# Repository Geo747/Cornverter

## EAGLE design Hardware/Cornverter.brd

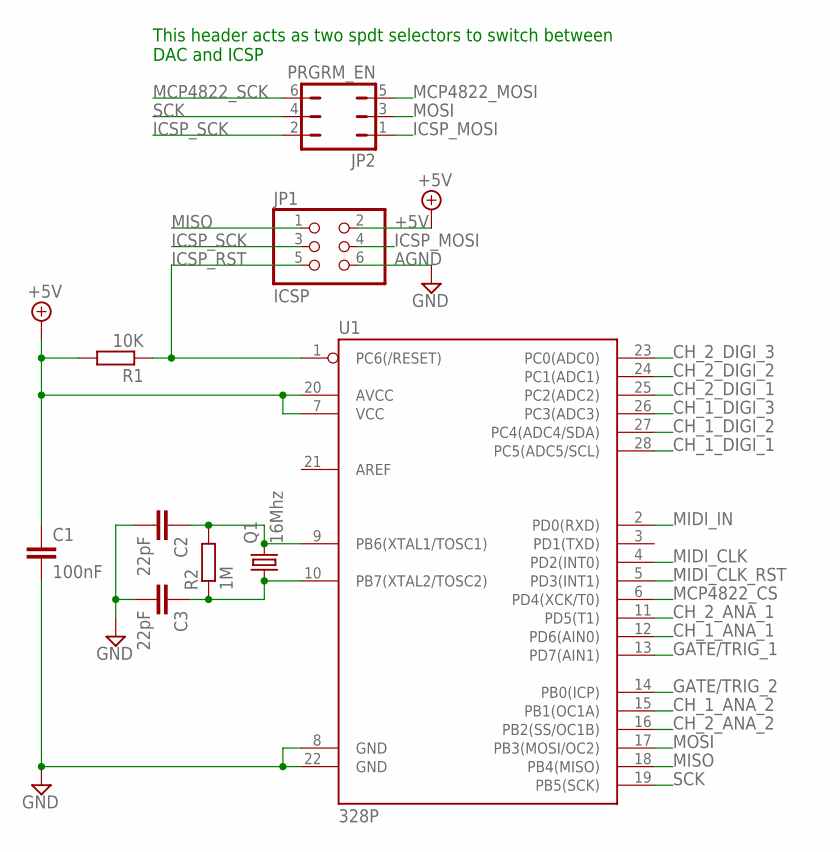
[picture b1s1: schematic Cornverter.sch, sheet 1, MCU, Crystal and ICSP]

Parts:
C1: 100nF; C1206
C2, C3: 22pF; C1206
JP1: ICSP; 2X03
JP2: PRGRM_EN; JP3Q
Q1: 16Mhz; HC49/S
R1: 10K; R1206
R2: 1M; R1206
U1: 328P; DIP28

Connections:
+5V: C1.1, JP1.2, R1.2, U1.7 (VCC), U1.20 (AVCC); also elsewhere on the board
AGND: C1.2, C2.2, C3.2, JP1.6, U1.8 (GND), U1.22 (GND); also elsewhere on the board
CH_1_ANA_1: U1.12 (PD6(AIN0)); also elsewhere on the board
CH_1_ANA_2: U1.15 (PB1(OC1A)); also elsewhere on the board
CH_1_DIGI_1: U1.28 (PC5(ADC5/SCL)); also elsewhere on the board
CH_1_DIGI_2: U1.27 (PC4(ADC4/SDA)); also elsewhere on the board
CH_1_DIGI_3: U1.26 (PC3(ADC3)); also elsewhere on the board
CH_2_ANA_1: U1.11 (PD5(T1)); also elsewhere on the board
CH_2_ANA_2: U1.16 (PB2(SS/OC1B)); also elsewhere on the board
CH_2_DIGI_1: U1.25 (PC2(ADC2)); also elsewhere on the board
CH_2_DIGI_2: U1.24 (PC1(ADC1)); also elsewhere on the board
CH_2_DIGI_3: U1.23 (PC0(ADC0)); also elsewhere on the board
GATE/TRIG_1: U1.13 (PD7(AIN1)); also elsewhere on the board
GATE/TRIG_2: U1.14 (PB0(ICP)); also elsewhere on the board
ICSP_MOSI: JP1.4, JP2.1
ICSP_RST: JP1.5, R1.1, U1.1 (PC6(/RESET))
ICSP_SCK: JP1.3, JP2.2
MCP4822_CS: U1.6 (PD4(XCK/T0)); also elsewhere on the board
MCP4822_MOSI: JP2.5; also elsewhere on the board
MCP4822_SCK: JP2.6; also elsewhere on the board
MIDI_CLK: U1.4 (PD2(INT0)); also elsewhere on the board
MIDI_CLK_RST: U1.5 (PD3(INT1)); also elsewhere on the board
MIDI_IN: U1.2 (PD0(RXD)); also elsewhere on the board
MISO: JP1.1, U1.18 (PB4(MISO))
MOSI: JP2.3, U1.17 (PB3(MOSI/OC2))
unnamed: C3.1, Q1.1, R2.1, U1.10 (PB7(XTAL2/TOSC2))
unnamed: C2.1, Q1.2, R2.2, U1.9 (PB6(XTAL1/TOSC1))
SCK: JP2.4, U1.19 (PB5(SCK))

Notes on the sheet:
This header acts as two spdt selectors to switch between DAC and ICSP

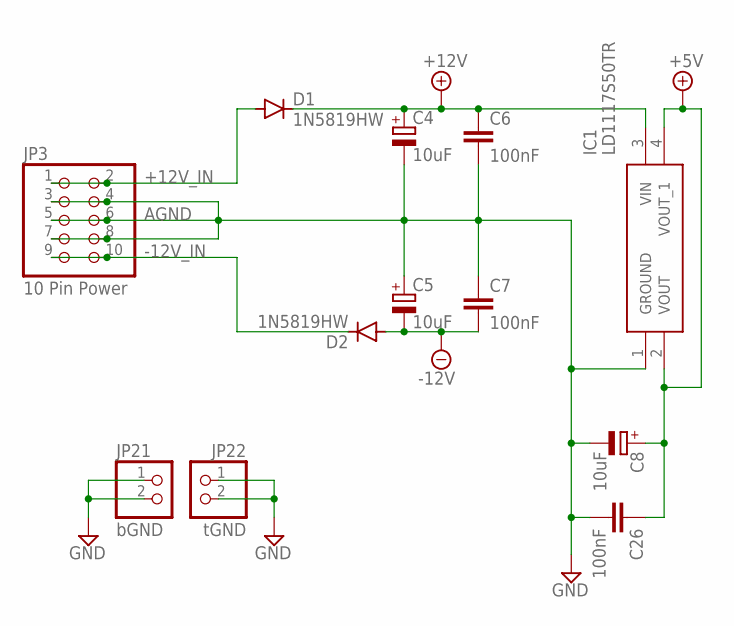
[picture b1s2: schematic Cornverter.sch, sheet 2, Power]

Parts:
C4, C5, C8: 10uF; E2-5
C6, C7, C26: 100nF; C1206
D1, D2: 1N5819HW; SOD123
IC1: LD1117S50TR; SOT230P700X190-4N
JP3: 10 Pin Power; 2X05
JP21: bGND; 1X02
JP22: tGND; 1X02

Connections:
+5V: C8.+, C26.1, IC1.2 (VOUT), IC1.4 (VOUT_1); also elsewhere on the board
+12V: C4.+, C6.1, D1.C, IC1.3 (VIN); also elsewhere on the board
+12V_IN: D1.A, JP3.1, JP3.2
-12V: C5.-, C7.2, D2.A; also elsewhere on the board
-12V_IN: D2.C, JP3.9, JP3.10
AGND: C4.-, C5.+, C6.2, C7.1, C8.-, C26.2, IC1.1 (GROUND), JP3.3, JP3.4, JP3.5, JP3.6, JP3.7, JP3.8, JP21.1, JP21.2, JP22.1, JP22.2; also elsewhere on the board

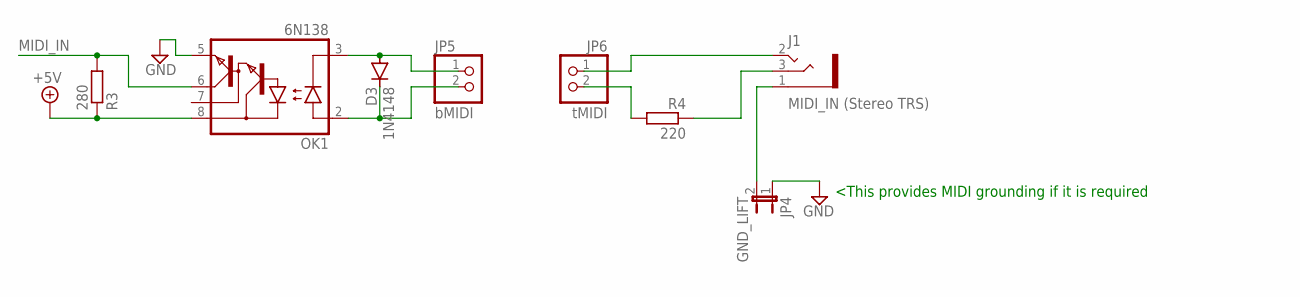
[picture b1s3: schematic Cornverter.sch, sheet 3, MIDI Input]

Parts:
D3: 1N4148; DO35-7
J1: MIDI_IN (Stereo TRS); WQP-PJ301M-12-ST_JACK
JP4: GND_LIFT; JP1
JP5: bMIDI; 1X02
JP6: tMIDI; 1X02
OK1: 6N138; DIL08
R3: 280; R1206
R4: 220; R1206

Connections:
+5V: OK1.8 (VCC), R3.1; also elsewhere on the board
AGND: JP4.1, OK1.5 (GND); also elsewhere on the board
MIDI_IN: OK1.6 (VO), R3.2; also elsewhere on the board
unnamed: J1.1, JP4.2
unnamed: J1.3, R4.1
unnamed: D3.A, JP5.1, OK1.3 (C)
unnamed: D3.C, JP5.2, OK1.2 (A)
unnamed: JP6.2, R4.2
unnamed: J1.2, JP6.1

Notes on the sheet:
<This provides MIDI grounding if it is required

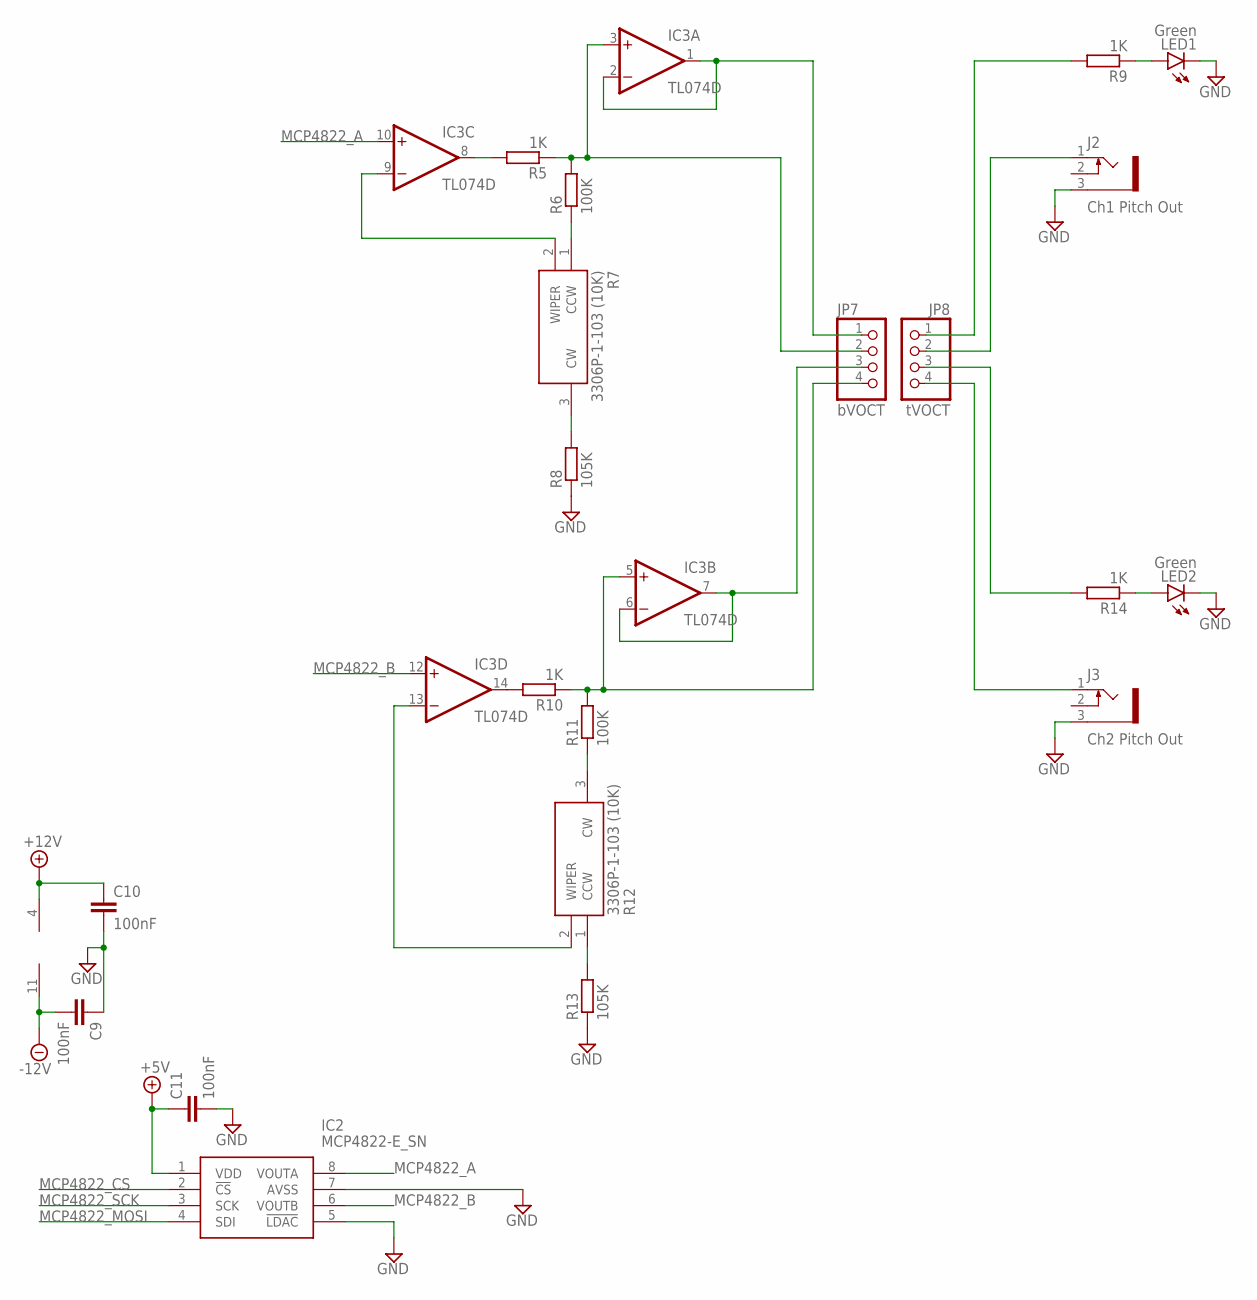
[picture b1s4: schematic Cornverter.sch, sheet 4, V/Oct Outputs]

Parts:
C9, C10, C11: 100nF; C1206
IC2: MCP4822-E_SN; SOIC127P600X175-8N
IC3: TL074D; SO14
J2: Ch1 Pitch Out; WQP-PJ301M-12_JACK
J3: Ch2 Pitch Out; WQP-PJ301M-12_JACK
JP7: bVOCT; 1X04
JP8: tVOCT; 1X04
LED1, LED2: Green; LED3MM
R5, R9, R10, R14: 1K; R1206
R6, R11: 100K; R1206
R7, R12: 3306P-1-103 (10K); 3306P1103
R8, R13: 105K; R1206

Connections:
+5V: C11.1, IC2.1 (VDD); also elsewhere on the board
+12V: C10.1, IC3.4 (V+); also elsewhere on the board
-12V: C9.2, IC3.11 (V-); also elsewhere on the board
AGND: C9.1, C10.2, C11.2, IC2.5 (!LDAC), IC2.7 (AVSS), J2.3 (1), J3.3 (1), LED1.C, LED2.C, R8.1, R13.1; also elsewhere on the board
MCP4822_A: IC2.8 (VOUTA), IC3.10 (+IN)
MCP4822_B: IC2.6 (VOUTB), IC3.12 (+IN)
MCP4822_CS: IC2.2 (!CS); also elsewhere on the board
MCP4822_MOSI: IC2.4 (SDI); also elsewhere on the board
MCP4822_SCK: IC2.3 (SCK); also elsewhere on the board
unnamed: R6.1, R7.1 (CCW)
unnamed: R7.3 (CW), R8.2
unnamed: R12.1 (CCW), R13.2
unnamed: R11.1, R12.3 (CW)
unnamed: LED1.A, R9.1
unnamed: IC3.1 (OUT), IC3.2 (-IN), JP7.1
unnamed: LED2.A, R14.1
unnamed: IC3.6 (-IN), IC3.7 (OUT), JP7.3
unnamed: IC3.9 (-IN), R7.2 (WIPER)
unnamed: IC3.3 (+IN), JP7.2, R5.1, R6.2
unnamed: IC3.13 (-IN), R12.2 (WIPER)
unnamed: IC3.5 (+IN), JP7.4, R10.1, R11.2
unnamed: IC3.14 (OUT), R10.2
unnamed: IC3.8 (OUT), R5.2
unnamed: JP8.1, R9.2
unnamed: J2.1 (2), JP8.2
unnamed: JP8.3, R14.2
unnamed: J3.1 (2), JP8.4

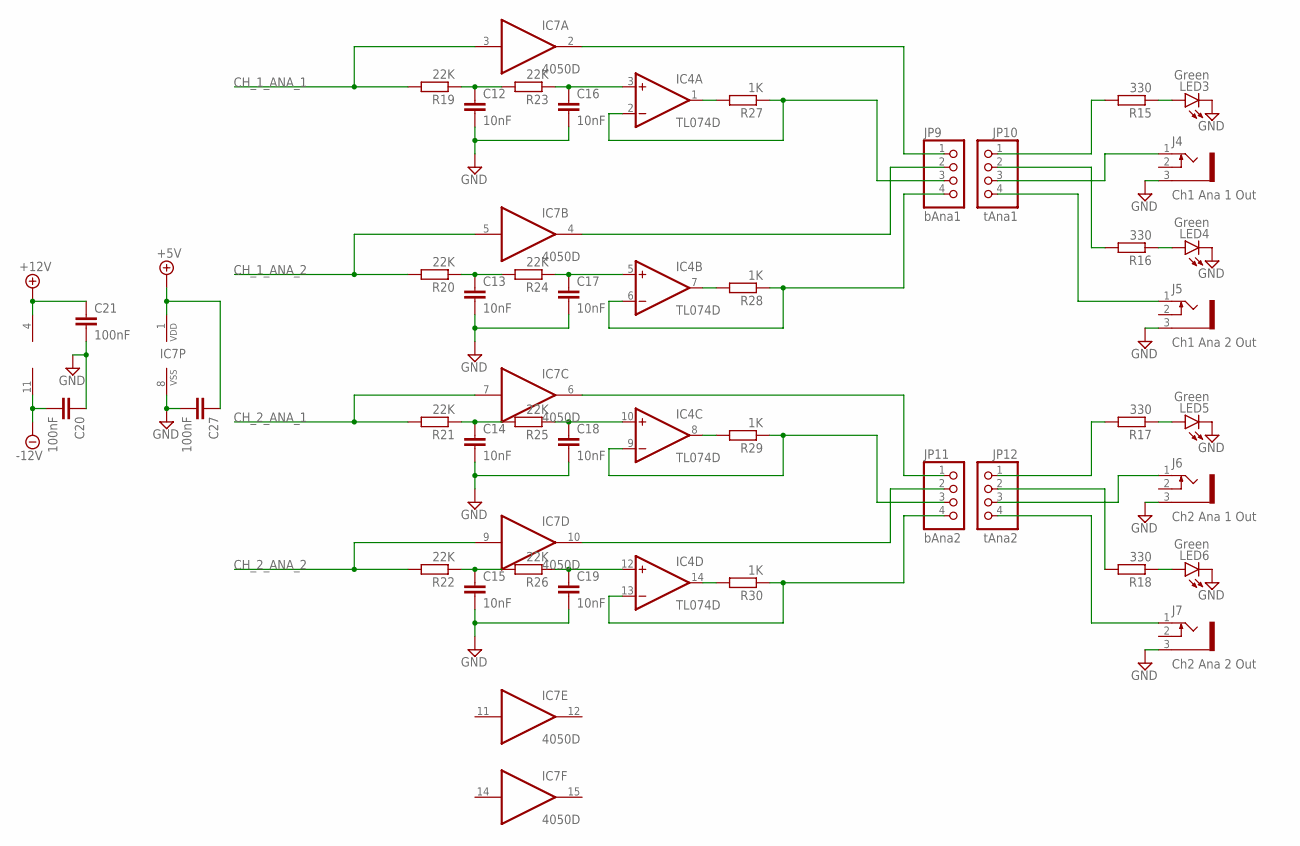
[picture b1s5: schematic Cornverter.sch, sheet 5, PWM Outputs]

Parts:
C12, C13, C14, C15, C16, C17, C18, C19: 10nF; C1206
C20, C21, C27: 100nF; C1206
IC4: TL074D; SO14
IC7: 4050D; SO16
J4: Ch1 Ana 1 Out; WQP-PJ301M-12_JACK
J5: Ch1 Ana 2 Out; WQP-PJ301M-12_JACK
J6: Ch2 Ana 1 Out; WQP-PJ301M-12_JACK
J7: Ch2 Ana 2 Out; WQP-PJ301M-12_JACK
JP9: bAna1; 1X04
JP10: tAna1; 1X04
JP11: bAna2; 1X04
JP12: tAna2; 1X04
LED3, LED4, LED5, LED6: Green; LED3MM
R15, R16, R17, R18: 330; R1206
R19, R20, R21, R22, R23, R24, R25, R26: 22K; R1206
R27, R28, R29, R30: 1K; R1206

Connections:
+5V: C27.1, IC7.1 (VDD); also elsewhere on the board
+12V: C21.1, IC4.4 (V+); also elsewhere on the board
-12V: C20.2, IC4.11 (V-); also elsewhere on the board
AGND: C12.2, C13.2, C14.2, C15.2, C16.2, C17.2, C18.2, C19.2, C20.1, C21.2, C27.2, IC7.8 (VSS), J4.3 (1), J5.3 (1), J6.3 (1), J7.3 (1), LED3.C, LED4.C, LED5.C, LED6.C; also elsewhere on the board
CH_1_ANA_1: IC7.3 (I), R19.2; also elsewhere on the board
CH_1_ANA_2: IC7.5 (I), R20.2; also elsewhere on the board
CH_2_ANA_1: IC7.7 (I), R21.2; also elsewhere on the board
CH_2_ANA_2: IC7.9 (I), R22.2; also elsewhere on the board
unnamed: C13.1, R20.1, R24.2
unnamed: LED4.A, R16.1
unnamed: IC4.6 (-IN), JP9.4, R28.1
unnamed: C12.1, R19.1, R23.2
unnamed: LED3.A, R15.1
unnamed: IC4.7 (OUT), R28.2
unnamed: C17.1, IC4.5 (+IN), R24.1
unnamed: IC4.1 (OUT), R27.2
unnamed: C14.1, R21.1, R25.2
unnamed: LED5.A, R17.1
unnamed: IC4.9 (-IN), JP11.3, R29.1
unnamed: IC4.8 (OUT), R29.2
unnamed: C16.1, IC4.3 (+IN), R23.1
unnamed: C18.1, IC4.10 (+IN), R25.1
unnamed: C15.1, R22.1, R26.2
unnamed: LED6.A, R18.1
unnamed: IC4.13 (-IN), JP11.4, R30.1
unnamed: IC4.14 (OUT), R30.2
unnamed: IC4.2 (-IN), JP9.3, R27.1
unnamed: C19.1, IC4.12 (+IN), R26.1
unnamed: JP10.1, R15.2
unnamed: J4.1 (2), JP10.3
unnamed: J5.1 (2), JP10.4
unnamed: JP12.1, R17.2
unnamed: JP12.2, R18.2
unnamed: J6.1 (2), JP12.3
unnamed: J7.1 (2), JP12.4
unnamed: JP10.2, R16.2
unnamed: IC7.2 (O), JP9.1
unnamed: IC7.4 (O), JP9.2
unnamed: IC7.6 (O), JP11.1
unnamed: IC7.10 (O), JP11.2

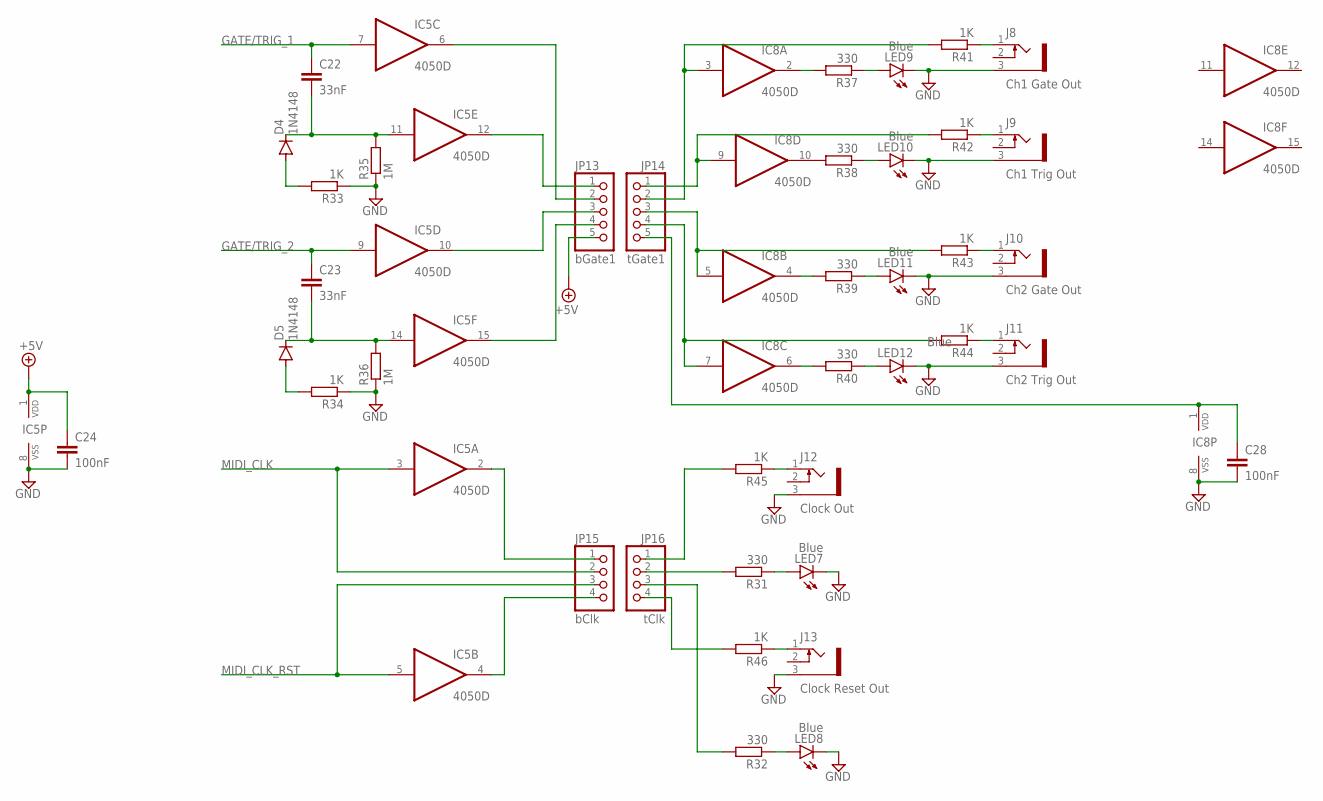
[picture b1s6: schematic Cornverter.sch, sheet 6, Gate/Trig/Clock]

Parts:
C22, C23: 33nF; C1206
C24, C28: 100nF; C1206
D4, D5: 1N4148; DO35-7
IC5, IC8: 4050D; SO16
J8: Ch1 Gate Out; WQP-PJ301M-12_JACK
J9: Ch1 Trig Out; WQP-PJ301M-12_JACK
J10: Ch2 Gate Out; WQP-PJ301M-12_JACK
J11: Ch2 Trig Out; WQP-PJ301M-12_JACK
J12: Clock Out; WQP-PJ301M-12_JACK
J13: Clock Reset Out; WQP-PJ301M-12_JACK
JP13: bGate1; 1X05
JP14: tGate1; 1X05
JP15: bClk; 1X04
JP16: tClk; 1X04
LED7, LED8, LED9, LED10, LED11, LED12: Blue; LED3MM
R31, R32, R37, R38, R39, R40: 330; R1206
R33, R34, R41, R42, R43, R44, R45, R46: 1K; R1206
R35, R36: 1M; R1206

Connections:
+5V: C24.1, IC5.1 (VDD), JP13.5; also elsewhere on the board
AGND: C24.2, C28.2, IC5.8 (VSS), IC8.8 (VSS), J8.3 (1), J9.3 (1), J10.3 (1), J11.3 (1), J12.3 (1), J13.3 (1), LED7.C, LED8.C, LED9.C, LED10.C, LED11.C, LED12.C, R33.1, R34.1, R35.1, R36.1; also elsewhere on the board
GATE/TRIG_1: C22.1, IC5.7 (I); also elsewhere on the board
GATE/TRIG_2: C23.1, IC5.9 (I); also elsewhere on the board
MIDI_CLK: IC5.3 (I), JP15.2; also elsewhere on the board
MIDI_CLK_RST: IC5.5 (I), JP15.3; also elsewhere on the board
unnamed: C22.2, D4.C, IC5.11 (I), R35.2
unnamed: D4.A, R33.2
unnamed: IC8.7 (I), JP14.4, R44.2
unnamed: LED12.A, R40.1
unnamed: LED11.A, R39.1
unnamed: IC8.5 (I), JP14.3, R43.2
unnamed: J11.1 (2), R44.1
unnamed: J10.1 (2), R43.1
unnamed: C23.2, D5.C, IC5.14 (I), R36.2
unnamed: D5.A, R34.2
unnamed: IC8.9 (I), JP14.1, R42.2
unnamed: LED10.A, R38.1
unnamed: LED9.A, R37.1
unnamed: IC8.3 (I), JP14.2, R41.2
unnamed: LED7.A, R31.1
unnamed: J12.1 (2), R45.1
unnamed: IC5.2 (O), JP15.1
unnamed: J13.1 (2), R46.1
unnamed: IC5.4 (O), JP15.4
unnamed: LED8.A, R32.1
unnamed: J9.1 (2), R42.1
unnamed: J8.1 (2), R41.1
unnamed: IC8.2 (O), R37.2
unnamed: IC5.6 (O), JP13.2
unnamed: IC5.12 (O), JP13.1
unnamed: IC5.15 (O), JP13.4
unnamed: IC5.10 (O), JP13.3
unnamed: JP16.1, R45.2
unnamed: JP16.2, R31.2
unnamed: JP16.4, R46.2
unnamed: JP16.3, R32.2
unnamed: IC8.10 (O), R38.2
unnamed: IC8.4 (O), R39.2
unnamed: IC8.6 (O), R40.2
TOP+5V: C28.1, IC8.1 (VDD), JP14.5

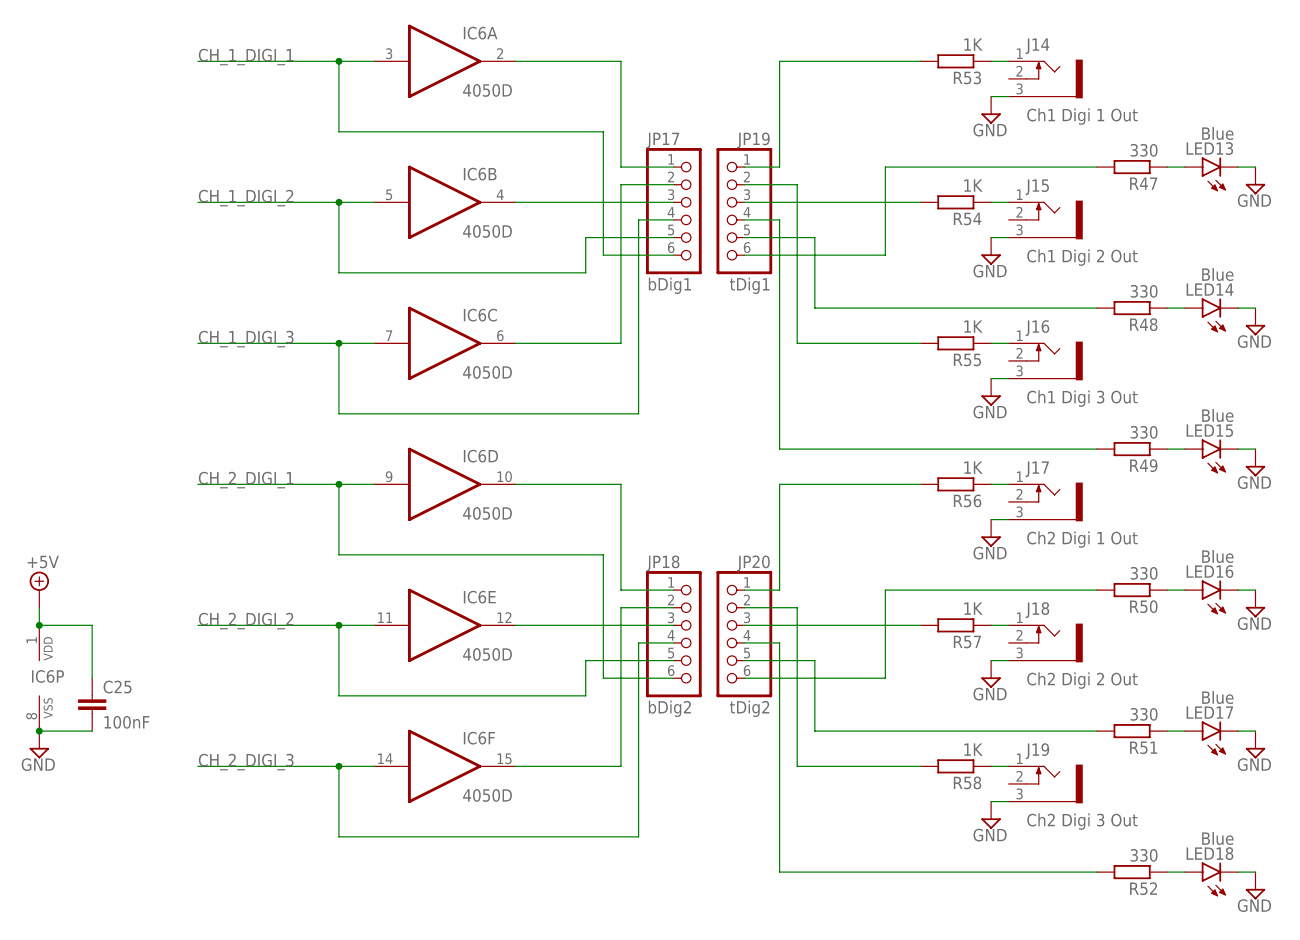
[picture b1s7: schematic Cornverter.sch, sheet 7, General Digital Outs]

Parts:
C25: 100nF; C1206
IC6: 4050D; SO16
J14: Ch1 Digi 1 Out; WQP-PJ301M-12_JACK
J15: Ch1 Digi 2 Out; WQP-PJ301M-12_JACK
J16: Ch1 Digi 3 Out; WQP-PJ301M-12_JACK
J17: Ch2 Digi 1 Out; WQP-PJ301M-12_JACK
J18: Ch2 Digi 2 Out; WQP-PJ301M-12_JACK
J19: Ch2 Digi 3 Out; WQP-PJ301M-12_JACK
JP17: bDig1; 1X06
JP18: bDig2; 1X06
JP19: tDig1; 1X06
JP20: tDig2; 1X06
LED13, LED14, LED15, LED16, LED17, LED18: Blue; LED3MM
R47, R48, R49, R50, R51, R52: 330; R1206
R53, R54, R55, R56, R57, R58: 1K; R1206

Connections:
+5V: C25.1, IC6.1 (VDD); also elsewhere on the board
AGND: C25.2, IC6.8 (VSS), J14.3 (1), J15.3 (1), J16.3 (1), J17.3 (1), J18.3 (1), J19.3 (1), LED13.C, LED14.C, LED15.C, LED16.C, LED17.C, LED18.C; also elsewhere on the board
CH_1_DIGI_1: IC6.3 (I), JP17.6; also elsewhere on the board
CH_1_DIGI_2: IC6.5 (I), JP17.5; also elsewhere on the board
CH_1_DIGI_3: IC6.7 (I), JP17.4; also elsewhere on the board
CH_2_DIGI_1: IC6.9 (I), JP18.6; also elsewhere on the board
CH_2_DIGI_2: IC6.11 (I), JP18.5; also elsewhere on the board
CH_2_DIGI_3: IC6.14 (I), JP18.4; also elsewhere on the board
unnamed: LED15.A, R49.1
unnamed: J16.1 (2), R55.1
unnamed: JP19.1, R53.2
unnamed: J17.1 (2), R56.1
unnamed: JP19.6, R47.2
unnamed: LED16.A, R50.1
unnamed: LED17.A, R51.1
unnamed: J18.1 (2), R57.1
unnamed: JP19.3, R54.2
unnamed: J19.1 (2), R58.1
unnamed: JP19.4, R49.2
unnamed: LED13.A, R47.1
unnamed: J14.1 (2), R53.1
unnamed: JP19.2, R55.2
unnamed: J15.1 (2), R54.1
unnamed: JP19.5, R48.2
unnamed: LED14.A, R48.1
unnamed: LED18.A, R52.1
unnamed: JP20.1, R56.2
unnamed: JP20.6, R50.2
unnamed: JP20.2, R58.2
unnamed: JP20.5, R51.2
unnamed: JP20.3, R57.2
unnamed: JP20.4, R52.2
unnamed: IC6.2 (O), JP17.1
unnamed: IC6.6 (O), JP17.2
unnamed: IC6.10 (O), JP18.1
unnamed: IC6.15 (O), JP18.2
unnamed: IC6.12 (O), JP18.3
unnamed: IC6.4 (O), JP17.3

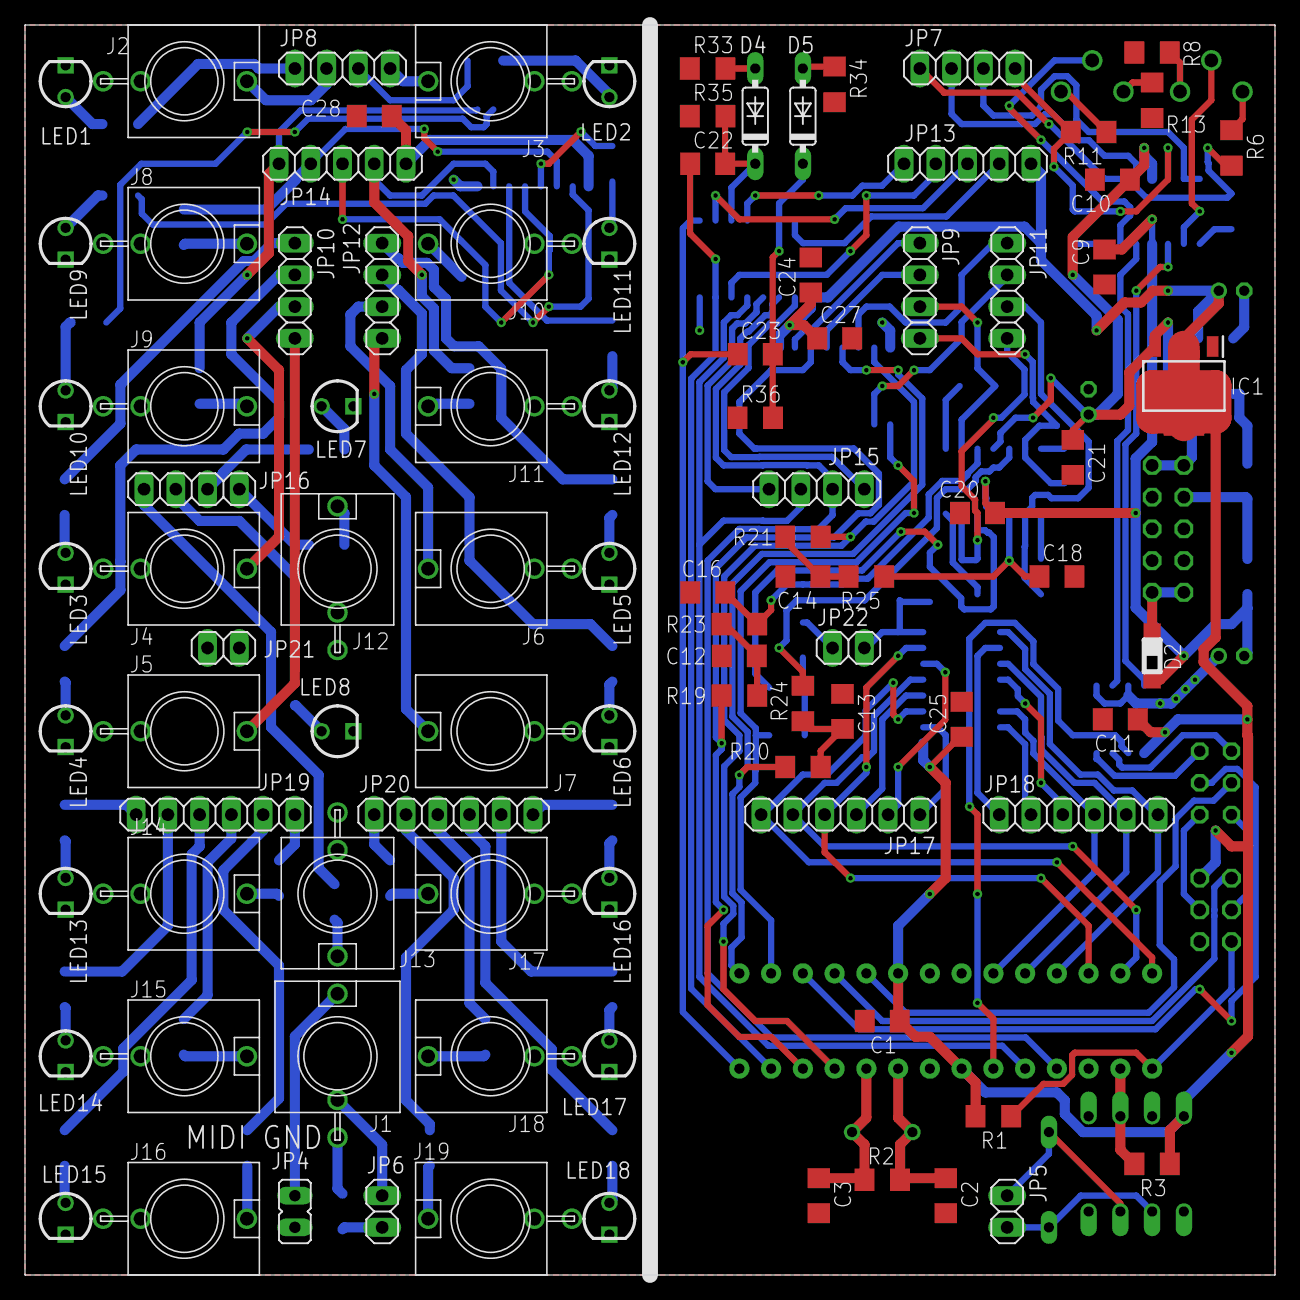
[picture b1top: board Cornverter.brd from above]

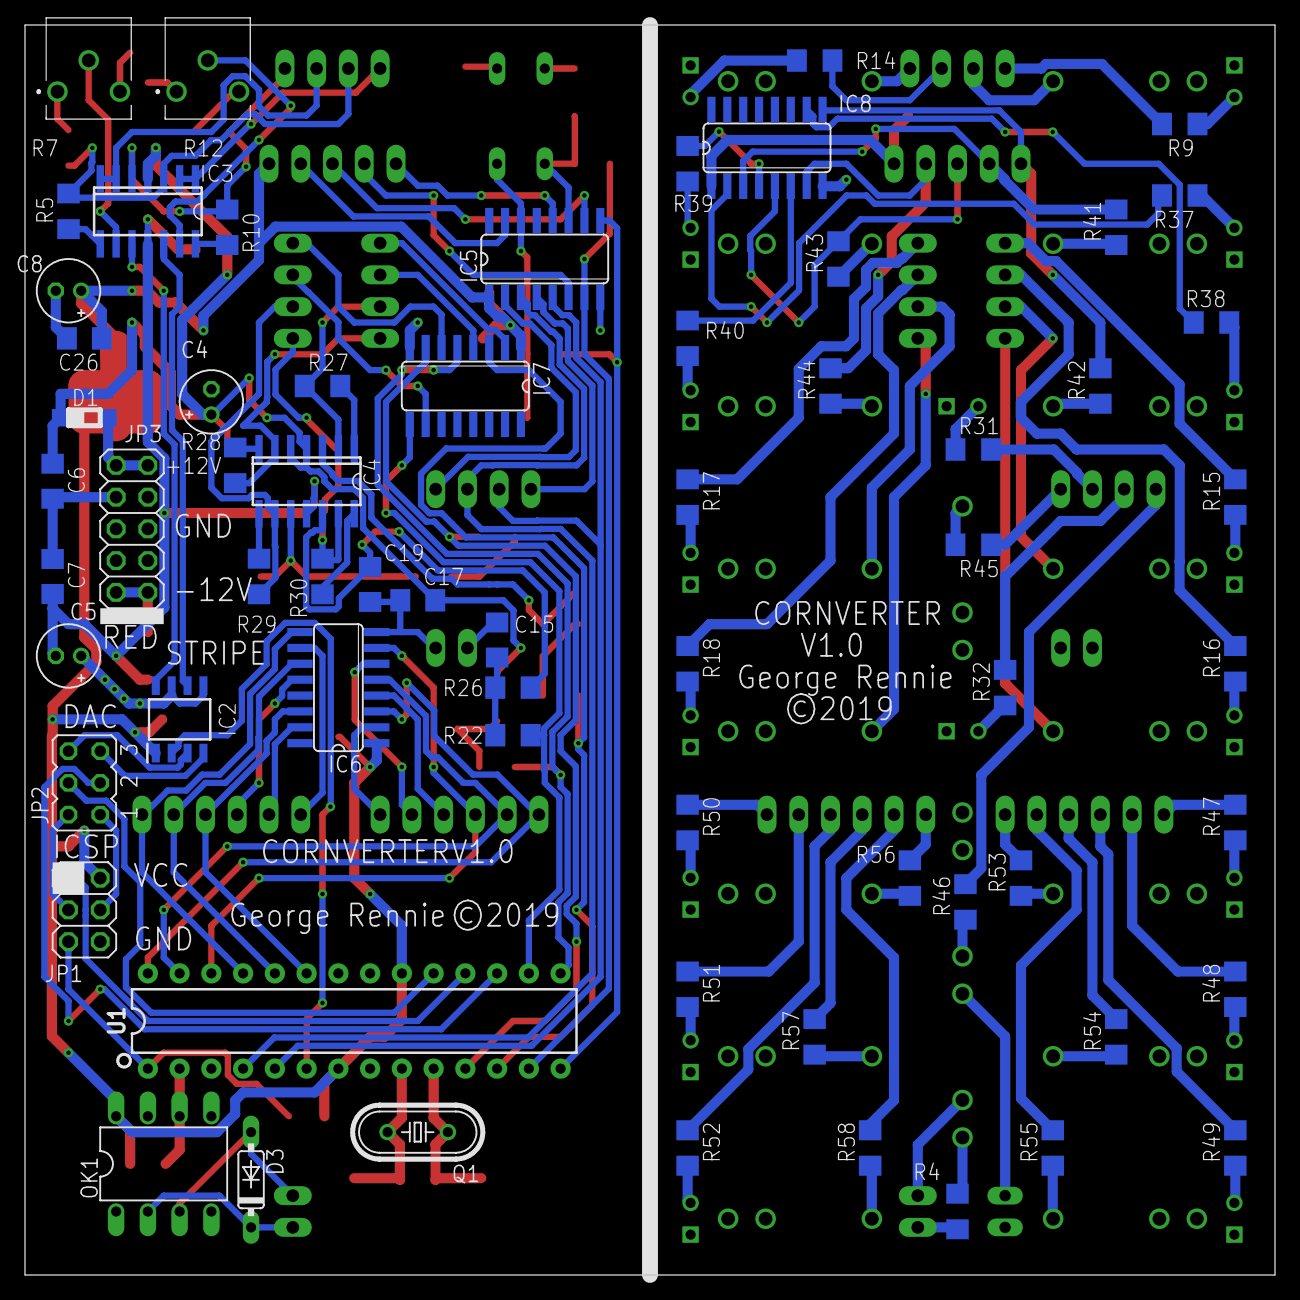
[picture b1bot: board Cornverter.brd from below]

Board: 2 copper layers, 100.0 x 100.0 mm, 161 parts (65 on the bottom side), 155 nets.

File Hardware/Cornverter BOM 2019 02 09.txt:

Qty	Value	Device	Package	Parts	Description	DESCRIPTION	HEIGHT	MANUFACTURER_NAME	MANUFACTURER_PART_NUMBER	MF	MOUSER_PART_NUMBER	MPN	OC_FARNELL	OC_NEWARK	PROD_ID	SPICEPREFIX	VALUE
1	bGND	PINHD-1X2	1X02	JP21	PIN HEADER												
1	bMIDI	PINHD-1X2	1X02	JP5	PIN HEADER												
1	tGND	PINHD-1X2	1X02	JP22	PIN HEADER												
1	tMIDI	PINHD-1X2	1X02	JP6	PIN HEADER												
1	bAna1	PINHD-1X4	1X04	JP9	PIN HEADER												
1	bAna2	PINHD-1X4	1X04	JP11	PIN HEADER												
1	bClk	PINHD-1X4	1X04	JP15	PIN HEADER												
1	bVOCT	PINHD-1X4	1X04	JP7	PIN HEADER												
1	tAna1	PINHD-1X4	1X04	JP10	PIN HEADER												
1	tAna2	PINHD-1X4	1X04	JP12	PIN HEADER												
1	tClk	PINHD-1X4	1X04	JP16	PIN HEADER												
1	tVOCT	PINHD-1X4	1X04	JP8	PIN HEADER												
1	bGate1	PINHD-1X5	1X05	JP13	PIN HEADER												
1	tGate1	PINHD-1X5	1X05	JP14	PIN HEADER												
1	bDig1	PINHD-1X6	1X06	JP17	PIN HEADER												
1	bDig2	PINHD-1X6	1X06	JP18	PIN HEADER												
1	tDig1	PINHD-1X6	1X06	JP19	PIN HEADER												
1	tDig2	PINHD-1X6	1X06	JP20	PIN HEADER												
1	ICSP	PINHD-2X3	2X03	JP1	PIN HEADER												
1	10 Pin Power	PINHD-2X5	2X05	JP3	PIN HEADER												
2	3306P-1-103 (10K)	3306P-1-103	3306P1103	"R7, R12"	"3306P 1-turn cermet trimmer,10K 300mW Bourns 3306P Series Through Hole Cermet Trimmer Resistor with Pin Terminations, 10k 25% 1/5W 250ppm/C Top Adjust"	"3306P 1-turn cermet trimmer,10K 300mW Bourns 3306P Series Through Hole Cermet Trimmer Resistor with Pin Terminations, 10k 25% 1/5W 250ppm/C Top Adjust"	8mm	Bourns	3306P-1-103		652-3306P-1-103						
13	100nF	C-EUC1206	C1206	"C1, C6, C7, C9, C10, C11, C20, C21, C24, C25, C27, C28, C26"	"CAPACITOR, European symbol"											C	
8	10nF	C-EUC1206	C1206	"C12, C13, C14, C15, C16, C17, C18, C19"	"CAPACITOR, European symbol"											C	
2	22pF	C-EUC1206	C1206	"C2, C3"	"CAPACITOR, European symbol"											C	
2	33nF	C-EUC1206	C1206	"C22, C23"	"CAPACITOR, European symbol"											C	
1	6N138	6N138	DIL08	OK1	MOTOROLA OPTO COUPLER					VISHAY/TELEFUNKEN		6N138	9860150	35K5294		X	
1	328P	ATMEGA328P_PDIP	DIP28	U1	Atmel 328P										IC-09136		328P
3	1N4148	1N4148DO35-7	DO35-7	"D3, D4, D5"	DIODE												
3	10uF	CPOL-EUE2-5	E2-5	"C4, C5, C8"	"POLARIZED CAPACITOR, European symbol"											C	
1	16Mhz	CRYSTALHC49S	HC49/S	Q1	CRYSTAL								1667008	unknown			
1	GND_LIFT	JP1E	JP1	JP4	JUMPER												
1	PRGRM_EN	JP3Q	JP3Q	JP2	JUMPER												
12	Blue	LED3MM	LED3MM	"LED7, LED8, LED9, LED10, LED11, LED12, LED13, LED14, LED15, LED16, LED17, LED18"	3MM LED with clearer silkscreen than stock												
6	Green	LED3MM	LED3MM	"LED1, LED2, LED3, LED4, LED5, LED6"	3MM LED with clearer silkscreen than stock												
2	100K	R-EU_R1206	R1206	"R6, R11"	"RESISTOR, European symbol"											R	
2	105K	R-EU_R1206	R1206	"R8, R13"	"RESISTOR, European symbol"											R	
1	10K	R-EU_R1206	R1206	R1	"RESISTOR, European symbol"												
22	1K	R-EU_R1206	R1206	"R5, R9, R10, R14, R27, R28, R29, R30, R33, R34, R41, R42, R43, R44, R45, R46, R53, R54, R55, R56, R57, R58"	"RESISTOR, European symbol"											R	
3	1M	R-EU_R1206	R1206	"R2, R35, R36"	"RESISTOR, European symbol"											R	
2	220	R-EU_R1206	R1206	"R3, R4"	"RESISTOR, European symbol"											R	
8	22K	R-EU_R1206	R1206	"R19, R20, R21, R22, R23, R24, R25, R26"	"RESISTOR, European symbol"											R	
16	330	R-EU_R1206	R1206	"R15, R16, R17, R18, R31, R32, R37, R38, R39, R40, R47, R48, R49, R50, R51, R52"	"RESISTOR, European symbol"											R	
2	TL074D	TL074D	SO14	"IC3, IC4"	OP AMP												
4	4050D	4050D	SO16	"IC5, IC6, IC7, IC8"	Hex non-inverting BUFFER												
2	1N5819HW	DIODE-SOD123	SOD123	"D1, D2"	DIODE												
1	MCP4822-E_SN	MCP4822-E_SN	SOIC127P600X175-8N	IC2	D/A Converter 12-Bit 2ch SPI SOIC8	D/A Converter 12-Bit 2ch SPI SOIC8	1.75mm	Microchip	MCP4822-E/SN		579-MCP4822-E/SN						
1	LD1117S50TR	LD1117S50TR	SOT230P700X190-4N	IC1	"LD1117S50TR, Low Dropout Voltage Regulator, 1.3A, 5 V 1%, 4-Pin SOT-223"	"LD1117S50TR, Low Dropout Voltage Regulator, 1.3A, 5 V 1%, 4-Pin SOT-223"	1.9mm	STMicroelectronics	LD1117S50TR		511-LD1117S50						
1	Ch1 Ana 1 Out	WQP-PJ301M-12_JACK	WQP-PJ301M-12_JACK	J4	Thonkiconn mono jack												
1	Ch1 Ana 2 Out	WQP-PJ301M-12_JACK	WQP-PJ301M-12_JACK	J5	Thonkiconn mono jack												
1	Ch1 Digi 1 Out	WQP-PJ301M-12_JACK	WQP-PJ301M-12_JACK	J14	Thonkiconn mono jack												
1	Ch1 Digi 2 Out	WQP-PJ301M-12_JACK	WQP-PJ301M-12_JACK	J15	Thonkiconn mono jack												
1	Ch1 Digi 3 Out	WQP-PJ301M-12_JACK	WQP-PJ301M-12_JACK	J16	Thonkiconn mono jack												
1	Ch1 Gate Out	WQP-PJ301M-12_JACK	WQP-PJ301M-12_JACK	J8	Thonkiconn mono jack												
1	Ch1 Pitch Out	WQP-PJ301M-12_JACK	WQP-PJ301M-12_JACK	J2	Thonkiconn mono jack												
1	Ch1 Trig Out	WQP-PJ301M-12_JACK	WQP-PJ301M-12_JACK	J9	Thonkiconn mono jack												
1	Ch2 Ana 1 Out	WQP-PJ301M-12_JACK	WQP-PJ301M-12_JACK	J6	Thonkiconn mono jack												
1	Ch2 Ana 2 Out	WQP-PJ301M-12_JACK	WQP-PJ301M-12_JACK	J7	Thonkiconn mono jack												
1	Ch2 Digi 1 Out	WQP-PJ301M-12_JACK	WQP-PJ301M-12_JACK	J17	Thonkiconn mono jack												
1	Ch2 Digi 2 Out	WQP-PJ301M-12_JACK	WQP-PJ301M-12_JACK	J18	Thonkiconn mono jack												
1	Ch2 Digi 3 Out	WQP-PJ301M-12_JACK	WQP-PJ301M-12_JACK	J19	Thonkiconn mono jack												
1	Ch2 Gate Out	WQP-PJ301M-12_JACK	WQP-PJ301M-12_JACK	J10	Thonkiconn mono jack												
1	Ch2 Pitch Out	WQP-PJ301M-12_JACK	WQP-PJ301M-12_JACK	J3	Thonkiconn mono jack												
1	Ch2 Trig Out	WQP-PJ301M-12_JACK	WQP-PJ301M-12_JACK	J11	Thonkiconn mono jack												
1	Clock Out	WQP-PJ301M-12_JACK	WQP-PJ301M-12_JACK	J12	Thonkiconn mono jack												
1	Clock Reset Out	WQP-PJ301M-12_JACK	WQP-PJ301M-12_JACK	J13	Thonkiconn mono jack												
1	MIDI_IN (Stereo TRS)	WQP-PJ301M-12-ST_JACK	WQP-PJ301M-12-ST_JACK	J1	Thonkiconn stereo jack

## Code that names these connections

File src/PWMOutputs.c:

//Copyright 2018 George Rennie
#include "PWMOutputs.h"

void pwmSetup(void) {
  //Pins PD5, PD6 use timer 0B and 0A respectively (Ana1Ch2 and Ana1Ch1)
  //Pins PB1, PB2 use timer 1A and 1B respectively (Ana2Ch1 and Ana2Ch2)

  TCCR0A |= (1 << COM0A1) | (1 << COM0B1); //this and lines below set compare output mode to non inverting and enable pwm
  TCCR1A |= (1 << COM1A1) | (1 << COM1B1);
  TCCR0A &= ~(1 << COM0A0) & ~(1 << COM0B0);
  TCCR1A &= ~(1 << COM1A0) & ~(1 << COM1B0);

  TCCR0A |= (1 << WGM00) | (1 << WGM01); //Set timer 0 to Fast PWM
  TCCR0B &= ~(1 << WGM02); 

  TCCR1A |= (1 << WGM10); //Set Timer 1 to 8 bit Fast PWM
  TCCR1A &= ~(1 << WGM11);
  TCCR1B |= (1 << WGM12);
  TCCR1B &= ~(1 << WGM13);

  TCCR0B |= (1 << CS00); //Set Timer 0 prescaler to clkio/1 i.e. 16Mhz
  TCCR0B &= ~(1 << CS01) & ~(1 << CS02);

  TCCR1B |= (1 << CS10); //Set Timer 1 prescaler to clkio/1 i.e. 16Mhz
  TCCR1B &= ~(1 << CS11) & ~(1 << CS12);

  OCR0A = 0x00; //Set all output compare registers to 0
  OCR0B = 0x00;
  OCR1AH = 0x00; //Timer 1 is 16 bit so has two ocr registers but as this program uses 8 bit pwm only so only the low byte should need to be written to
  OCR1AL = 0x00;
  OCR1BH = 0x00;
  OCR1BL = 0x00;
}

void pwmWrite(byte value, byte channel, byte output) { //Input value is 7 bit
  volatile uint8_t* OCR;
  switch (channel) {
    case 0:
      switch(output) {
        case 0:
          OCR = &OCR0A;
          break;
        case 1:
          OCR = &OCR1AL;
          break;
        default:
          return;
      }
      break;

    case 1:
      switch(output) {
        case 0:
          OCR = &OCR0B;
          break;
        case 1:
          OCR = &OCR1BL;
          break;
        default:
          return;
      }
      break;

    default:
      return;
  }

  value = value << 1; //Make Value use all 8 bits of range
  *OCR = value;
}

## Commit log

2018-10-24 :tada: Added .gitattributes
2018-10-24 Init
    Loaded basic vscode and makefile files
    TODO: Implement a uart midi read
2018-10-24 Basic serial read for midi working program turns on pin13 if it detects midi on messages and off for off message
2018-10-25 changed comments
2018-10-25 defined some basic defs and added MIDI_message struct
2018-10-25 setup basic data structures for MIDI lib
2018-10-25 TODO: create serial read lib then create parser
2018-10-25 added SerialRead library to read serial It uses interrupts and a ring buffer (32 byte default, changeable in settings.h) It can only perform reads not writes
2018-10-25 added missing semicolon so lib works fully now in theory
2018-10-25 Working MIDI reader that stores data in d.mMessage TODO: Make handler that calls different functions defined in main.c depending on message type
2018-10-25 Added Callbacks which should now work
2018-10-25 Slight problems with callback handler fixed to callbacks work fully now
2018-10-25 tidied files
2018-10-25 added PolyToMono library, untested
2018-10-25 PolyToMono working with small demo on pin 13
2018-10-26 stuff is working atm
2018-10-26 Basic digi writes created TODO:
2018-10-26 added TODO
2018-10-26 added ioPinsSettings to store all the iopins. This should be a much better solution for managing all the pins
2018-10-26 move isChannelUsed to MIDI.c
2018-10-26 added midi setup guide and made digi outputs work
2018-10-27 stuff
2018-10-27 Working analog pwm outputs implemented
2018-10-27 midi clock and reset working now
2018-10-27 added midi all note off message support
2019-01-04 Moved firmware to sub folder
2019-01-04 configured file structure and intellisense and git
2019-01-06 Added Spice Sims, now i need to implement the changes from these sims into the schematic and board
2019-01-06 added the changes from spice sims to the schematic
2019-01-07 updated board design for the changes to schematic and ran ERC and DRC
2019-02-09 Added BOM, about to check all components
2019-02-09 Excel BOM shows whole of schematic sheet 1 has been checked
2019-02-09 Changed +5V 10uF electrolytic's polarity to be correct
2019-02-09 Remove Eagle Backup Files
2019-02-09 Added 100nF bypass cap to 5V supply
2019-02-09 Checked Over all of schematic sheet 2: Power
2019-02-09 Changed value of R3 (on the MCU side of the 6n138) from 220 to 280 ohms as per midi spec
2019-02-09 Checked MIDI input page of schematic
2019-02-09 Checked V/oct outs page and happy
2019-02-09 Checked over schematic sheet 3 PWM outputs
2019-02-09 Removed unneeded spice files
2019-02-09 Fixed led resistor value in midi clock outputs spice sim
2019-02-09 Checked PWM Outputs page of schematic
2019-02-09 removed build and bin firmware folders from repo
2019-02-09 Finished checking entire schematic for design errors
2019-02-09 Added Name/Date/Copyright/Revnumber to PCBs
2019-02-10 Created New Gerber files
2019-02-10 Created full BOM
2019-02-10 Changed lcsc part number for 33nF cap
2019-02-10 Corrected price of cd4050 in bom
2019-02-10 Added ebay burchase to excel
2019-02-10 Forgot to save before previous commit
2019-02-10 forgot to save before previous commit again whoops
2019-02-11 Added jumpers to BOM
2019-02-12 Added LCSC and JLC purchases to BOM
2019-02-12 Added Thonk order to BOM file
2019-02-23 Updated makefile for avrisp mk2
2019-02-23 Added BOM for soldering
2019-02-23 Moved channel is in range from polytomono to main.c
2019-02-23 Changed indenting to 2 spaces
2019-02-23 Added MCP4822 Pins to ioPinsSettings
2019-02-24 Fixed serialread to use full buffer
2019-02-24 Added MCP4822 Basic control code which is working
2019-02-24 updated settings to include all file associations
2019-02-24 Removed mAccuracy and added protection from value input overflow in MCP4822 files
2019-02-24 syntax changes
2019-02-24 Implemented Voct outputs with adjustable accuracy
2019-04-12 removed vscode
2019-04-12 set baudrate to midi baudrate
2019-04-12 .gitignore fix
2019-04-15 Updated PWMOutputs so they can go down fully to 0V also cleaned code slightly
2019-04-18 Added basic pitch bend only has range of +-12 semitones right now which needs fixing
2019-04-18 Fixed subtraction bug in pitch bend code
2019-04-18 removed unneccessary returns from polytomono.c
2019-04-19 fixed bitwise to logical & in polytomono.c
2019-04-19 changed byte to uint8_t in polytomono.c
2019-04-19 Fixed bug with notes staying on in polytomono.c
2019-04-19 added note about problem fix not being needed in polytomono.c
2019-04-19 Put gate change before pitch change in midi note off
2019-04-19 changed voct.c so pitch bend is stored the way it will be received
2019-04-19 removed byte datatype replaced with uint8_t
2019-04-19 Added Pitchbend range RPN support This also involved creating an RPN handler
2019-04-19 Added way to set Ana2 outputs to velocity control
2019-04-19 added TODO to MCP4822.c
2019-04-19 Moved note range saved vars from voct to settings
2019-04-19 added ignoring notes outside current range
2019-04-19 added clock divider midi cc functionality
2019-04-20 added ioPinsWrite() to simplify writing to io
2019-04-20 updated digitaloutputs to useiopinswrite also got rid of ugly case statements
2019-04-20 updated ioPinsSettings to use ioPinsWrite
2019-04-20 updated comments in main.c
2019-04-20 Updated copyright year to 2019
2019-04-20 updated MCP4822.c to use ioPinsWrite
2019-04-20 tidied comments in MIDIMessage.h
2019-04-20 Added function comments to DigitalOutputs.h
2019-04-20 removed case statement in ioPinsSettings.c
2019-04-20 added comments to ioPinsSettings
2019-04-20 made all lines less than 80 chars in DigitalOutputs.c
2019-04-20 Added comments to main.c
2019-04-20 made all lines less than 80 chars in main.c
2019-04-20 added MCP4822 comments
2019-04-20 Added comments to MIDI.h and MIDI.c also fixed bug in isChannelMessage() used by running status
2019-04-20 fixed MIDIDefs.h comments
2019-04-20 removed channelInRange() from main.c This is not neccessary as this checking is done in MIDI.c
2019-04-20 removed defines from midi.c to midi.h
2019-04-20 added comments to PolyToMono.c and .h
2019-04-20 added comments to PWMOutputs
2019-04-20 added comments to SerialRead
2019-04-20 cleaned up comments in Settings.h
2019-04-20 Added comments to voct
2019-04-20 Fixed bug in MCP4822.c accuracy code
2019-04-20 Fixed incorrect initial pitchbend in Voct.c
2019-04-21 Added function call to polyToMonoSetAccuracy when accuracy is changed
2019-04-21 updated channelIsUsed check to only check if message is a channel message
2019-04-23 removed channel text from front panel
2020-04-07 Added support for offest midi channel range
2020-04-08 Revert "Added support for offest midi channel range"
    This reverts commit d7d07a08d3b94ab5cc78a3508a96c4663c482369.
2020-04-08 Added support for different midi channel ranges
2020-04-08 Added JSFX Plugin
2020-04-08 Set default midi channel offset to 0
2020-04-08 Added JSFX support for incoming midi
2020-04-08 Fixed channel offset bug for channelless messages
2020-04-08 Added support for setting midi offset on command line
2020-04-08 Fixed jsfx bug
2020-04-08 Added MIDI thru to jsfx
2020-11-09 Modified makefile for linux
2020-11-09 Updated gitignore
2020-11-09 updated commenting style

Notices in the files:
Hardware/Cornverter.brd:
©2019
parts and their libraries:
SparkFun-IC-Microcontroller: Licensing: Creative Commons ShareAlike 4.0 International - https://creativecommons.org/licenses/by-sa/4.0
